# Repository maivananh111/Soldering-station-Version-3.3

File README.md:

# Soldering-station-Version-3.3
Pcb và code cho trạm hàn 4 tỷ.
Phần cứng:
  - STM32F103C8T6
  - TFT LCD 1.8 inch ST7735
  - W25Q32
Phần mềm:

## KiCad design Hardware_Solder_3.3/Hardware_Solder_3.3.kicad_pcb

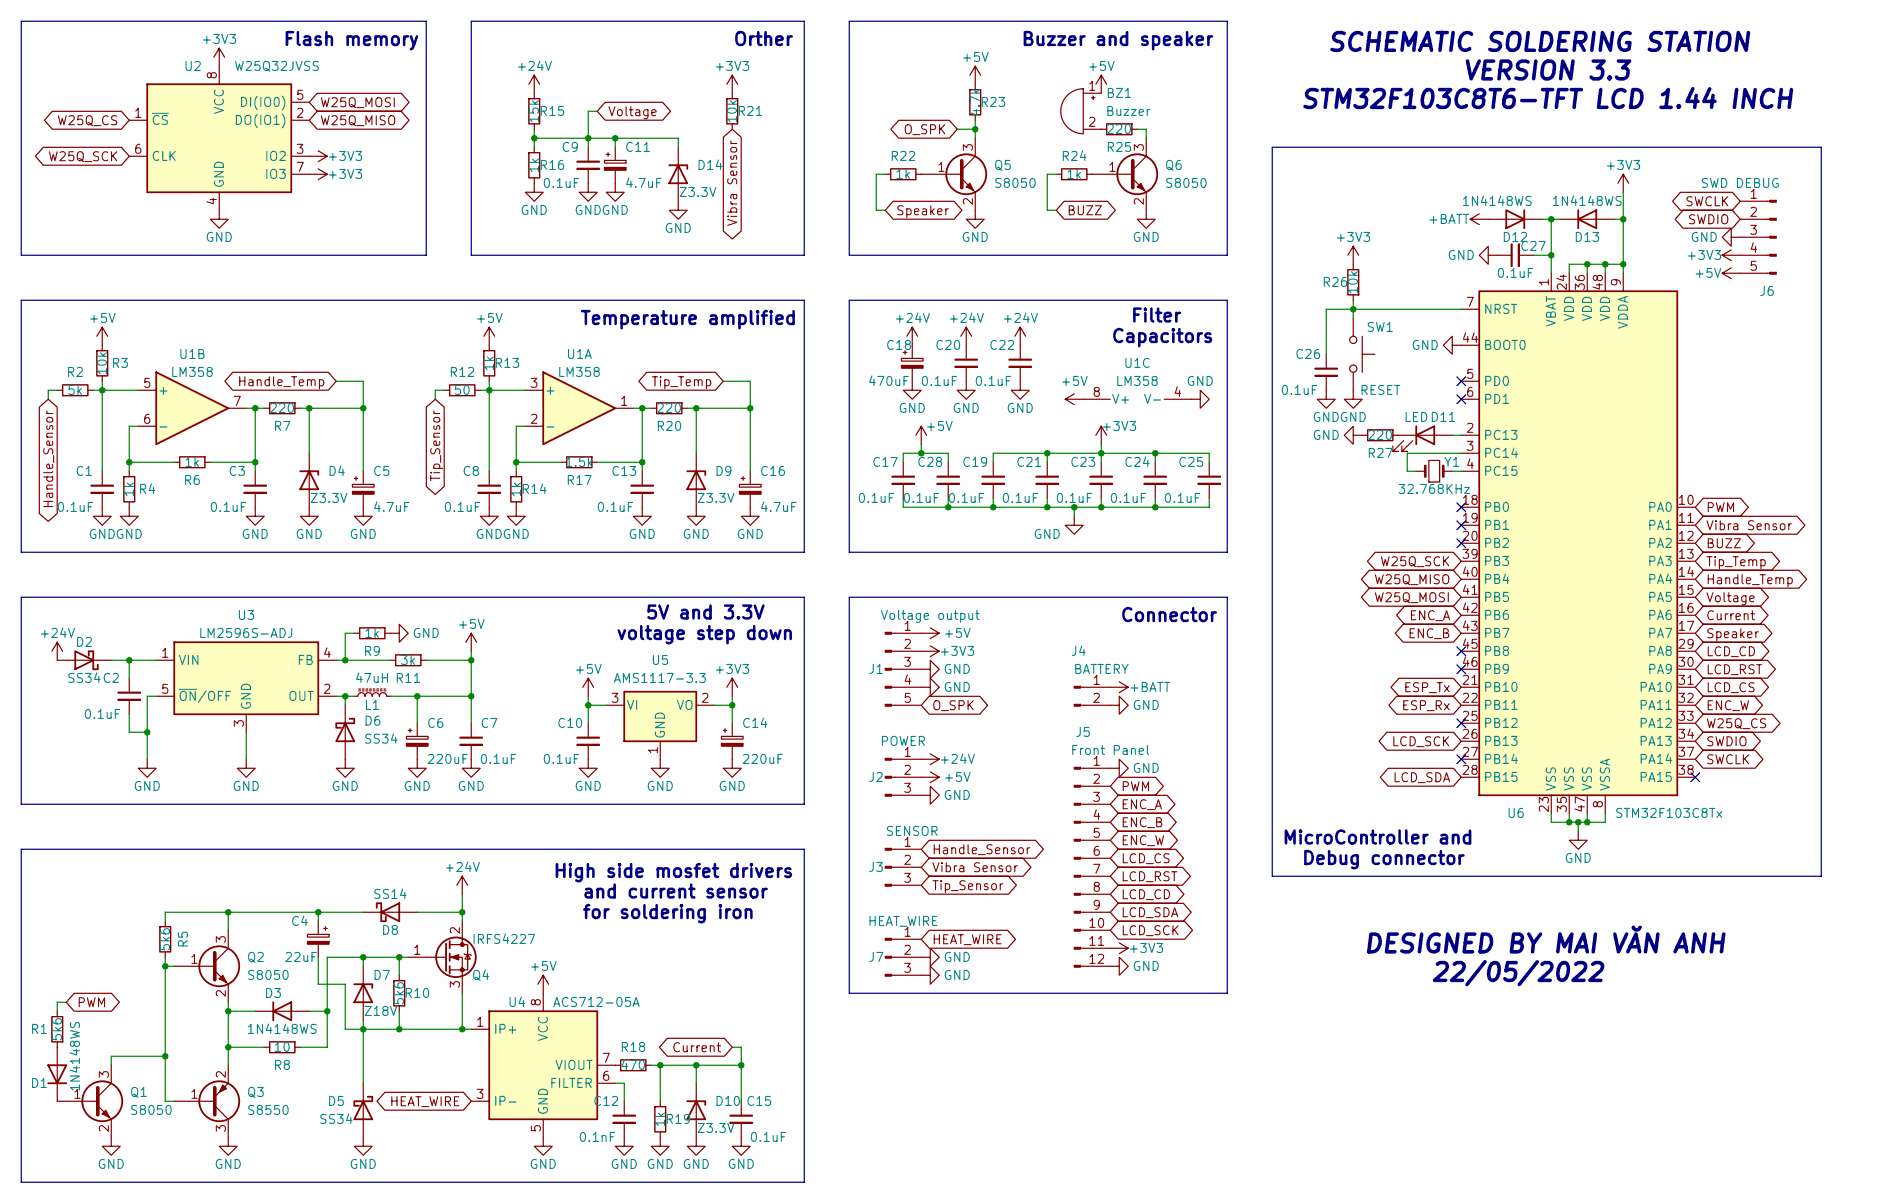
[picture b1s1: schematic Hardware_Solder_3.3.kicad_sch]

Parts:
BZ1: Buzzer; MagneticBuzzer_ProSignal_ABT-410-RC
C1, C2, C3, C7, C8, C9, C10, C13, C15, C17, C19, C20, C21, C22, C23, C24, C25, C26, C27, C28: 0.1uF; C_0603_1608Metric
C4: 22uF; CP_EIA-7343-43_Kemet-X
C5, C11, C16: 4.7uF; CP_EIA-3216-12_Kemet-S
C6, C14: 220uF; CP_Elec_6.3x7.7
C12: 0.1nF; C_0603_1608Metric
C18: 470uF; C_Radial_D10.0mm_H20.0mm_P5.00mm
D1, D3, D12, D13: 1N4148WS; D_SOD-323
D2, D5, D6: SS34; D_SMA
D4, D9, D10, D14: Z3.3V; D_MiniMELF
D7: Z18V; D_MiniMELF
D8: SS14; D_SMA
D11: LED; LED_0603_1608Metric
J1: Voltage output; PinHeader_1x05_P2.54mm_Vertical_SMD_Pin1Left
J2: POWER; JST_VH_B3PS-VH_1x03_P3.96mm_Horizontal
J3: SENSOR; PinHeader_1x03_P2.54mm_Vertical_SMD_Pin1Left
J4: BATTERY; PinHeader_1x02_P2.54mm_Vertical_SMD_Pin1Right
J5: Front Panel; PinHeader_1x12_P2.54mm_Vertical_SMD_Pin1Right
J6: SWD DEBUG; PinHeader_1x05_P2.54mm_Vertical_SMD_Pin1Right
J7: HEAT_WIRE; JST_VH_B3PS-VH_1x03_P3.96mm_Horizontal
L1: 47uH; L_12x12mm_H8mm
Q1, Q2, Q5, Q6: S8050; SOT-23
Q3: S8550; SOT-23
Q4: IRFS4227; TO-263-2
R1: 5k6; C_0603_1608Metric
R2: 5k; R_0603_1608Metric
R3, R21, R26: 10k; R_0603_1608Metric
R4, R6, R9, R13, R14, R16, R19, R22, R24: 1k; R_0603_1608Metric
R5, R10: 5k6; R_0603_1608Metric
R7, R20, R25, R27: 220; R_0603_1608Metric
R8: 10; R_0603_1608Metric
R11: 3k; R_0603_1608Metric
R12: 50; R_0603_1608Metric
R15: 15k; R_0603_1608Metric
R17: 1.5k; R_0603_1608Metric
R18: 470; R_0603_1608Metric
R23: 4.7k; R_0603_1608Metric
SW1: RESET; SW_SPST_CK_RS282G05A3
U1: LM358; SOIC-8_3.9x4.9mm_P1.27mm
U2: W25Q32JVSS; SOIC-8_5.23x5.23mm_P1.27mm
U3: LM2596S-ADJ; TO-263-5_TabPin3
U4: ACS712-05A; SOIC-8_3.9x4.9mm_P1.27mm
U5: AMS1117-3.3; SOT-223-3_TabPin2
U6: STM32F103C8Tx; LQFP-48_7x7mm_P0.5mm
Y1: 32.768KHz; Crystal_C38-LF_D3.0mm_L8.0mm_Horizontal_1EP_style1

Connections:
+3V3: C14.1, C19.1, C21.1, C23.1, C24.1, C25.1, D13.2 (A), J1.2, J5.11, J6.4, R21.1, R26.2, U2.3 (IO2), U2.7 (IO3), U2.8 (VCC), U5.2 (VO), U6.9 (VDDA), U6.24 (VDD), U6.36 (VDD), U6.48 (VDD)
+5V: BZ1.1 (-), C6.1, C7.1, C10.1, C17.1, C28.1, J1.1, J2.2, J6.5, L1.2, R3.1, R11.1, R13.1, R23.1, U1.8 (V+), U4.8 (VCC), U5.3 (VI)
+24V: C18.1, C20.1, C22.1, D2.2 (A), D8.2 (A), J2.1, Q4.2 (D), R15.1
+BATT: D12.2 (A), J4.1
BUZZ: R24.1, U6.12 (PA2)
Current: C15.1, D10.1 (K), R18.2, R19.1, U6.16 (PA6)
ENC_A: J5.3, U6.42 (PB6)
ENC_B: J5.4, U6.43 (PB7)
ENC_W: J5.5, U6.32 (PA11)
ESP_Rx: U6.22 (PB11)
ESP_Tx: U6.21 (PB10)
GND: C1.2, C2.2, C3.2, C5.2, C6.2, C7.2, C8.2, C9.2, C10.2, C11.2, C12.2, C13.2, C14.2, C15.2, C16.2, C17.2, C18.2, C19.2, C20.2, C21.2, C22.2, C23.2, C24.2, C25.2, C26.2, C27.1, C28.2, D4.2 (A), D5.2 (A), D6.2 (A), D9.2 (A), D10.2 (A), D14.2 (A), J1.3, J1.4, J2.3, J4.2, J5.1, J5.12, J6.3, J7.2, J7.3, Q1.2 (E), Q3.3 (C), Q5.2 (E), Q6.2 (E), R4.2, R9.1, R14.2, R16.2, R19.2, R27.2, SW1.2, U1.4 (V-), U2.4 (GND), U3.3 (GND), U3.5 (~ON/OFF), U4.5 (GND), U5.1 (GND), U6.8 (VSSA), U6.23 (VSS), U6.35 (VSS), U6.44 (BOOT0), U6.47 (VSS)
HEAT_WIRE: J7.1, U4.3 (IP-), U4.4 (IP-)
Handle_Sensor: J3.1, R2.1
Handle_Temp: C5.1, D4.1 (K), R7.1, U6.14 (PA4)
LCD_CD: J5.8, U6.29 (PA8)
LCD_CS: J5.6, U6.31 (PA10)
LCD_RST: J5.7, U6.30 (PA9)
LCD_SCK: J5.10, U6.26 (PB13)
LCD_SDA: J5.9, U6.28 (PB15)
unnamed: BZ1.2 (+), R25.2
unnamed: C1.1, R2.2, R3.2, U1.5 (+)
unnamed: C2.1, D2.1 (K), U3.1 (VIN)
unnamed: C3.1, R6.1, R7.2, U1.7
unnamed: C4.1, D8.1 (K), Q2.3 (C), R5.1
unnamed: C4.2, D5.1 (K), D7.2 (A), Q4.3 (S), R10.2, U4.1 (IP+), U4.2 (IP+)
unnamed: C8.1, R12.2, R13.2, U1.3 (+)
unnamed: C12.1, U4.6 (FILTER)
unnamed: C13.1, R17.1, R20.2, U1.1
unnamed: C26.1, R26.1, SW1.1, U6.7 (NRST)
unnamed: C27.2, D12.1 (K), D13.1 (K), U6.1 (VBAT)
unnamed: D1.1 (K), Q1.1 (B)
unnamed: D1.2 (A), R1.1
unnamed: D3.1 (K), Q2.2 (E), Q3.2 (E), R8.2
unnamed: D3.2 (A), D7.1 (K), Q4.1 (G), R8.1, R10.1
unnamed: D6.1 (K), L1.1, U3.2 (OUT)
unnamed: D11.1 (K), R27.1
unnamed: D11.2 (A), U6.2 (PC13)
unnamed: Q1.3 (C), Q2.1 (B), Q3.1 (B), R5.2
unnamed: Q5.1 (B), R22.2
unnamed: Q6.1 (B), R24.2
unnamed: Q6.3 (C), R25.1
unnamed: R4.1, R6.2, U1.6 (-)
unnamed: R9.2, R11.2, U3.4 (FB)
unnamed: R14.1, R17.2, U1.2 (-)
unnamed: R18.1, U4.7 (VIOUT)
unnamed: U6.3 (PC14), Y1.1
unnamed: U6.4 (PC15), Y1.2
O_SPK: J1.5, Q5.3 (C), R23.2
PWM: J5.2, R1.2, U6.10 (PA0)
SWCLK: J6.1, U6.37 (PA14)
SWDIO: J6.2, U6.34 (PA13)
Speaker: R22.1, U6.17 (PA7)
Tip_Sensor: J3.3, R12.1
Tip_Temp: C16.1, D9.1 (K), R20.1, U6.13 (PA3)
Vibra Sensor: J3.2, R21.2, U6.11 (PA1)
Voltage: C9.1, C11.1, D14.1 (K), R15.2, R16.1, U6.15 (PA5)
W25Q_CS: U2.1 (~CS), U6.33 (PA12)
W25Q_MISO: U2.2 (DO(IO1)), U6.40 (PB4)
W25Q_MOSI: U2.5 (DI(IO0)), U6.41 (PB5)
W25Q_SCK: U2.6 (CLK), U6.39 (PB3)

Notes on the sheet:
Temperature amplified
5V and 3.3V voltage step down
Connector
SCHEMATIC SOLDERING STATION VERSION 3.3 STM32F103C8T6-TFT LCD 1.44 INCH
Flash memory
Buzzer and speaker
DESIGNED BY MAI VĂN ANH 22/05/2022
Filter Capacitors
Orther
High side mosfet drivers and current sensor for soldering iron
MicroController and Debug connector

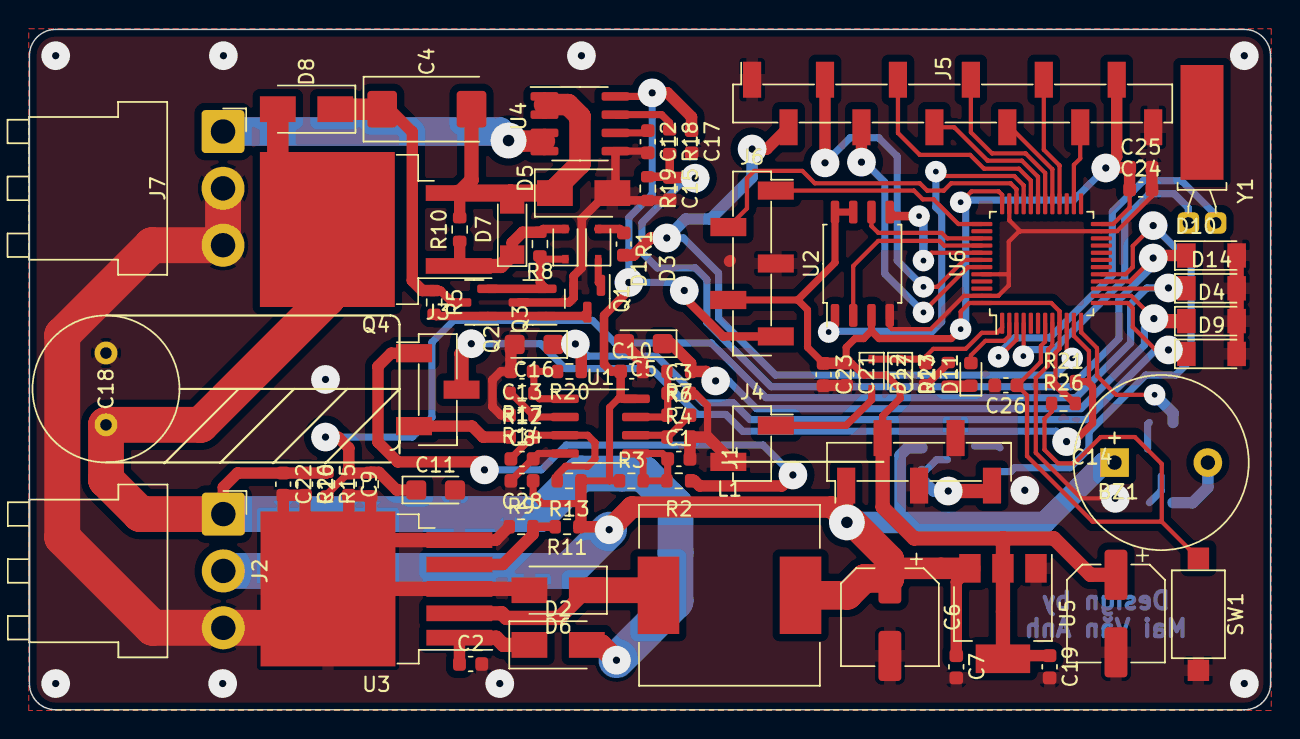
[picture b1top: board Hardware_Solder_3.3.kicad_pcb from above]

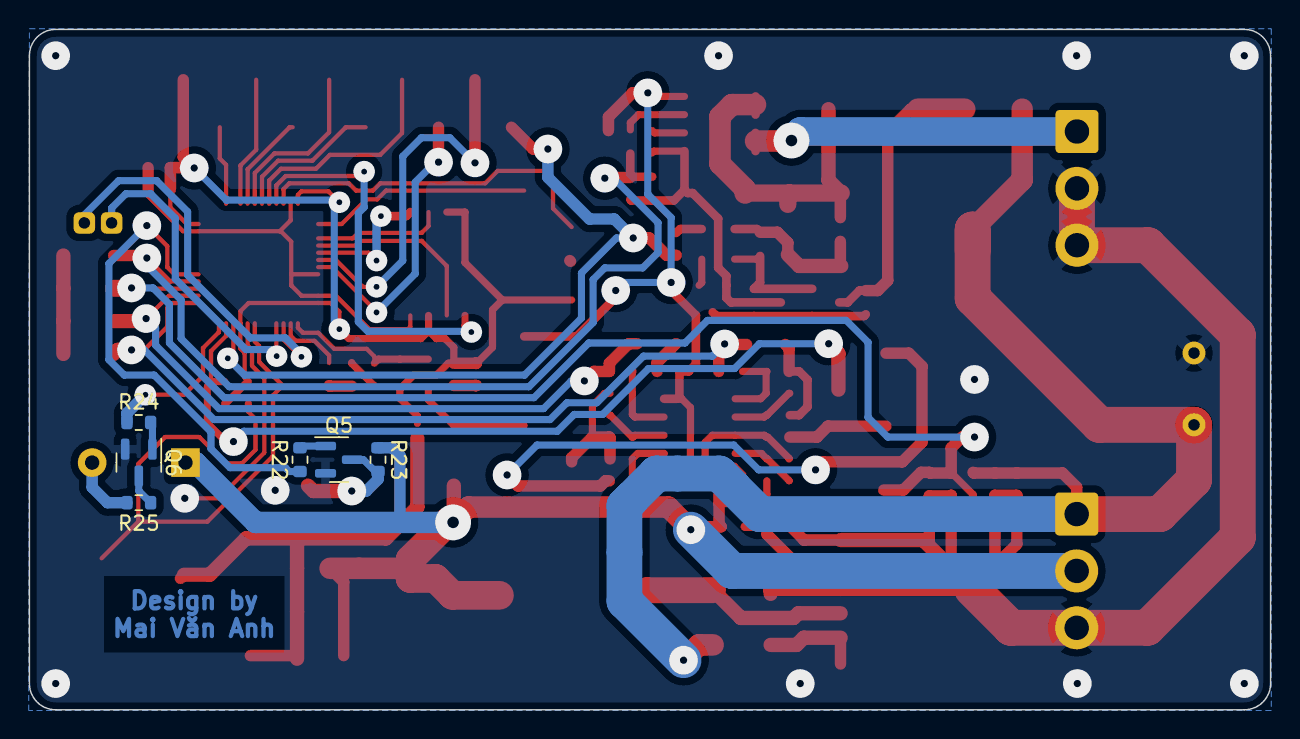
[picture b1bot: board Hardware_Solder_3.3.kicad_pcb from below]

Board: 2 copper layers, 86.5 x 47.4 mm, 92 parts (6 on the bottom side), 59 nets.
